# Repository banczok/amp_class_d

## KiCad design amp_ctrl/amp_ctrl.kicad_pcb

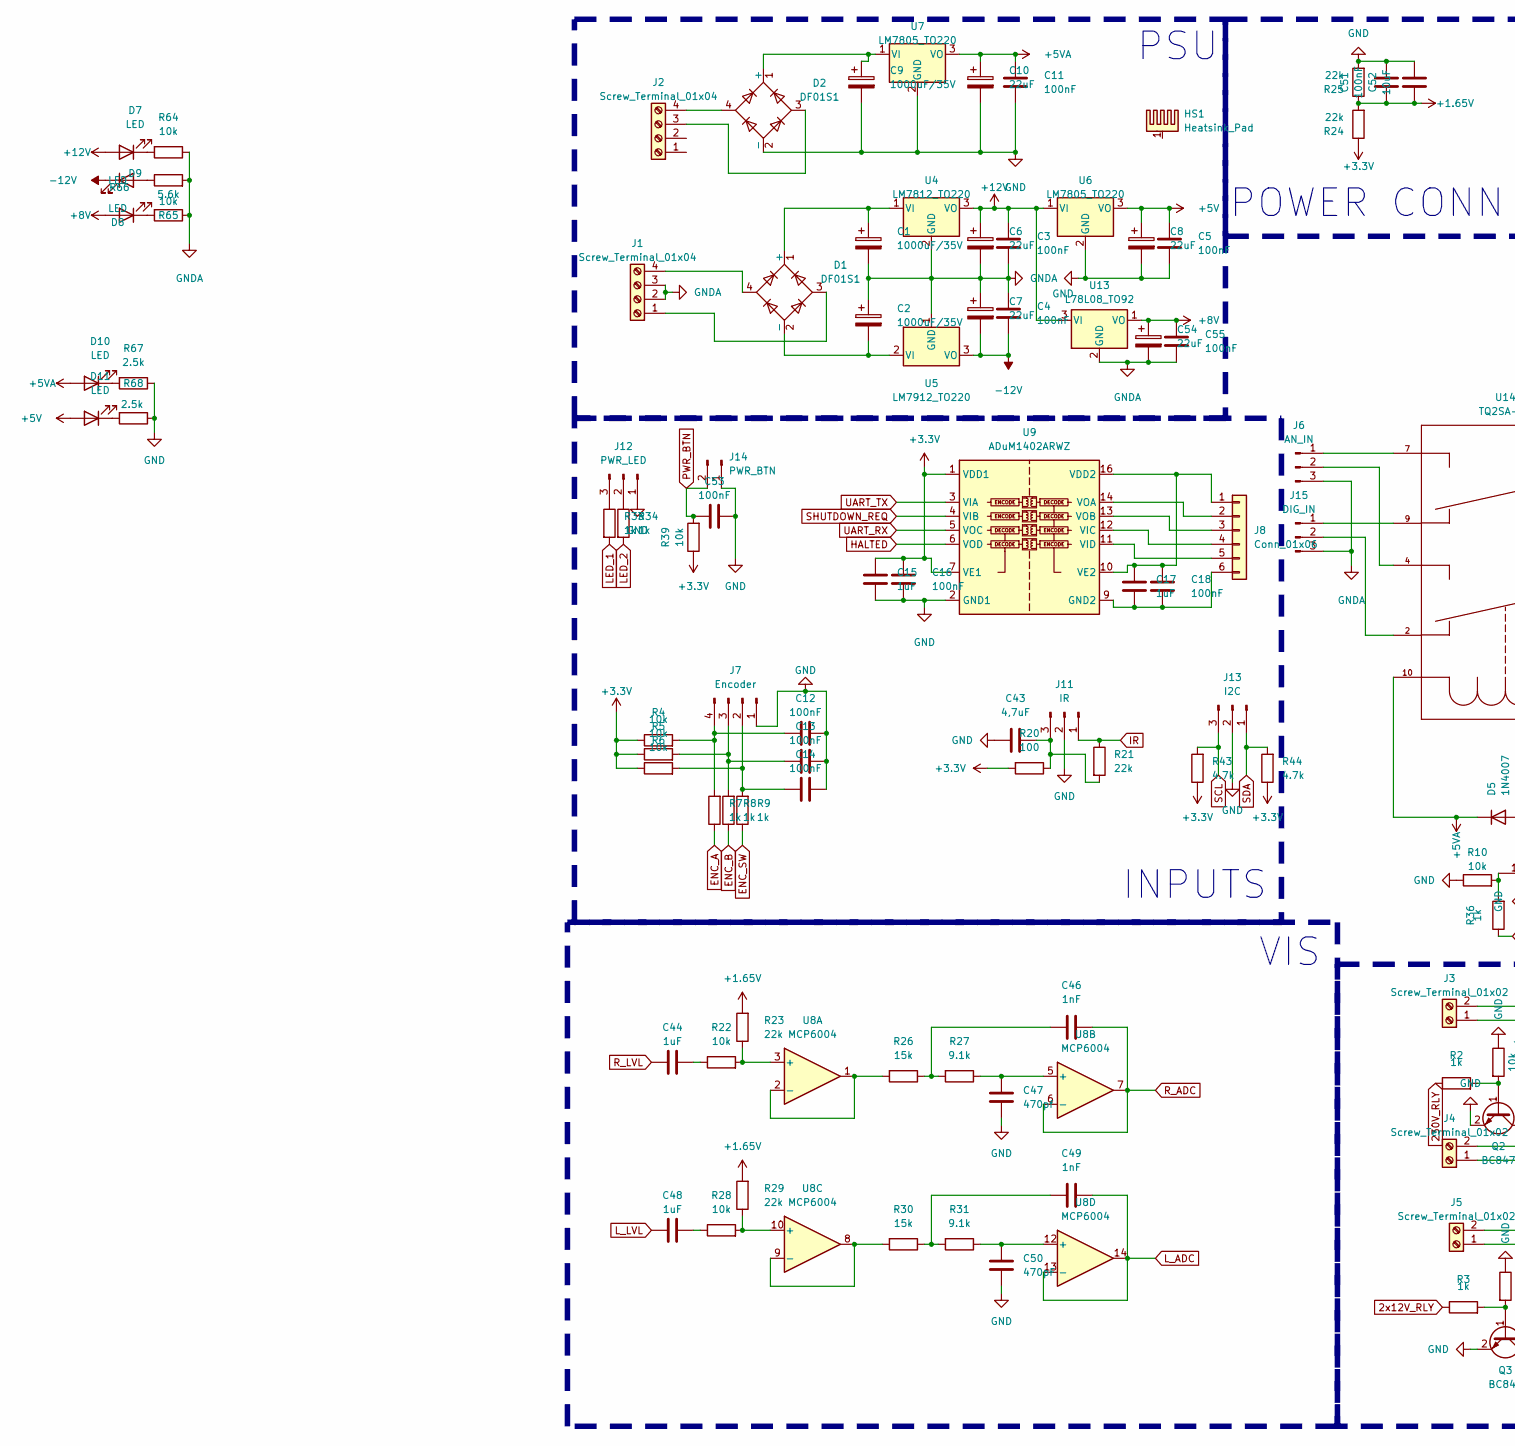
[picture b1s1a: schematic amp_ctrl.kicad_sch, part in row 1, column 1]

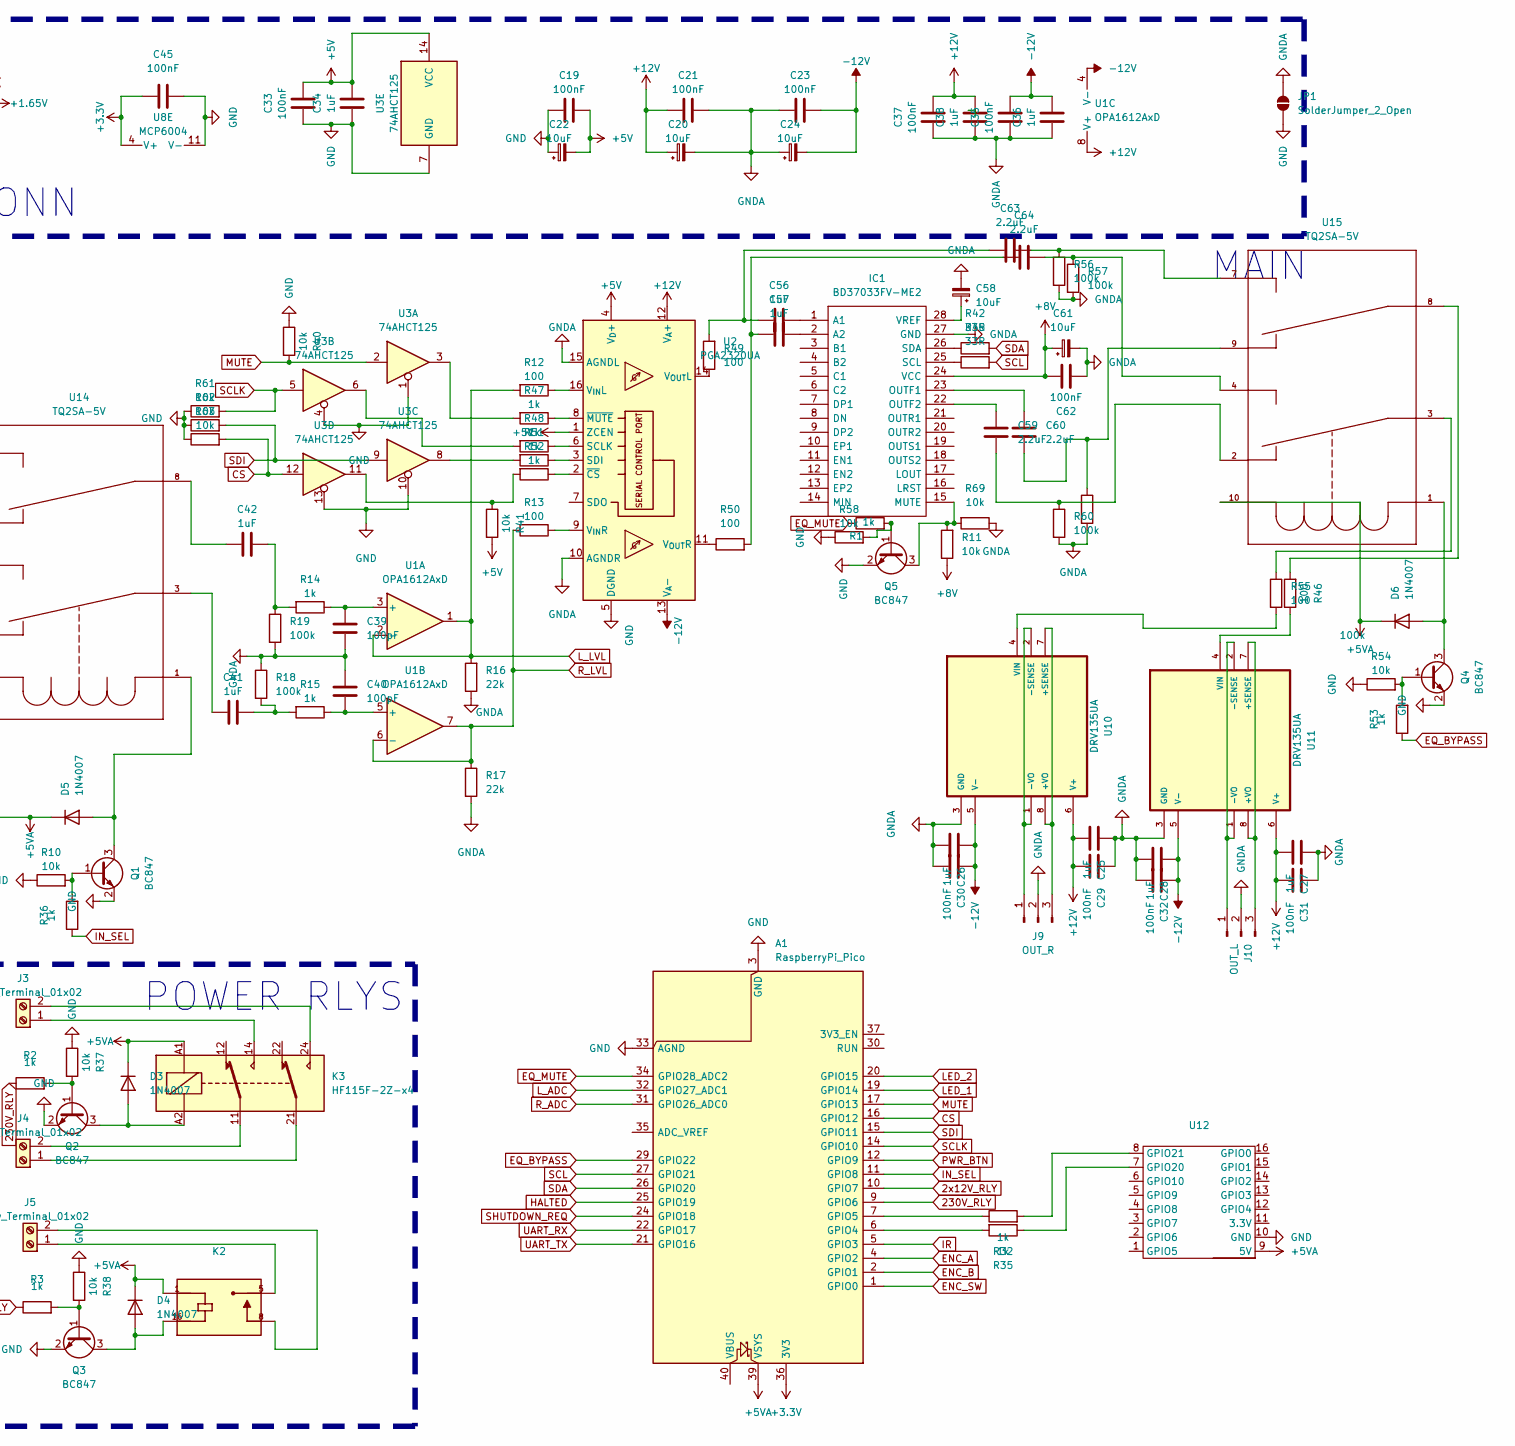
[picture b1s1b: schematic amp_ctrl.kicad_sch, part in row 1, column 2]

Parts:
A1: RaspberryPi_Pico; RaspberryPi_Pico_Common_SMD
C1, C2, C9: 1000uF/35V; CP_Radial_D12.5mm_P5.00mm
C3, C4, C5, C11, C12, C13, C14, C16, C18, C19, C21, C23, C29, C30, C31, C32, C33, C35, C37, C45, C51, C53, C55, C62: 100nF; C_0805_2012Metric_Pad1.18x1.45mm_HandSolder
C6, C7, C8, C10, C54: 22uF; CP_Radial_D5.0mm_P2.50mm
C15, C17, C25, C26, C27, C28, C34, C36, C38: 1uF; C_0805_2012Metric_Pad1.18x1.45mm_HandSolder
C20, C22, C24, C58, C61: 10uF; CP_EIA-6032-28_Kemet-C_Pad2.25x2.35mm_HandSolder
C39, C40: 100pF; C_0805_2012Metric_Pad1.18x1.45mm_HandSolder
C41, C42, C44, C48, C56, C57: 1uF; C_Disc_D8.0mm_W5.0mm_P5.00mm
C43: 4,7uF; C_0805_2012Metric_Pad1.18x1.45mm_HandSolder
C46, C49: 1nF; C_0805_2012Metric_Pad1.18x1.45mm_HandSolder
C47: 470pf; C_0805_2012Metric_Pad1.18x1.45mm_HandSolder
C50: 470pF; C_0805_2012Metric_Pad1.18x1.45mm_HandSolder
C52: 10uF; C_0805_2012Metric_Pad1.18x1.45mm_HandSolder
C59, C60, C63, C64: 2.2uF; C_Disc_D8.0mm_W5.0mm_P5.00mm
D1, D2: DF01S1; Diode_Bridge_OnSemi_SDIP-4L
D3, D4, D5, D6: 1N4007; D_DO-41_SOD81_P10.16mm_Horizontal
D7, D8, D9, D10, D11: LED; LED_1206_3216Metric_Pad1.42x1.75mm_HandSolder
HS1: Heatsink_Pad; Heatsink_Fischer_SK104-STC-STIC_35x13mm_2xDrill2.5mm
IC1: BD37033FV-ME2; SSOP-28_5.3x10.2mm_P0.65mm; Mouser Part Number 755-BD37033FV-ME2
J1, J2: Screw_Terminal_01x04; TerminalBlock_Phoenix_MKDS-1,5-4_1x04_P5.00mm_Horizontal
J3, J4, J5: Screw_Terminal_01x02; TerminalBlock_MaiXu_MX126-5.0-02P_1x02_P5.00mm
J6: AN_IN; PinHeader_1x03_P2.54mm_Vertical
J7: Encoder; PinHeader_1x04_P2.54mm_Vertical
J8: Conn_01x06; PinHeader_1x06_P2.54mm_Vertical
J9: OUT_R; PinHeader_1x03_P2.54mm_Vertical
J10: OUT_L; PinHeader_1x03_P2.54mm_Vertical
J11: IR; PinHeader_1x03_P2.54mm_Vertical
J12: PWR_LED; PinHeader_1x03_P2.54mm_Vertical
J13: I2C; PinHeader_1x03_P2.54mm_Vertical
J14: PWR_BTN; PinSocket_1x02_P2.54mm_Vertical
J15: DIG_IN; PinHeader_1x03_P2.54mm_Vertical
JP1: SolderJumper_2_Open; SolderJumper-2_P1.3mm_Open_Pad1.0x1.5mm
K2: PR30-12V-450-1A; RELAY_PR30-12V-450-1A; PARTREV 1.0
K3: HF115F-2Z-x4; Relay_DPDT_Finder_40.62
Q1, Q2, Q3, Q4, Q5: BC847; SOT-23
R1, R2, R3, R7, R8, R9, R14, R15, R32, R33, R34, R35, R36, R47, R48, R51, R52, R53: 1k; R_0805_2012Metric_Pad1.20x1.40mm_HandSolder
R4, R5, R6, R10, R11, R22, R28, R37, R38, R39, R40, R41, R54, R58, R61, R62, R63, R64, R65, R69: 10k; R_0805_2012Metric_Pad1.20x1.40mm_HandSolder
R12, R13, R20, R46, R49, R50, R55: 100; R_0805_2012Metric_Pad1.20x1.40mm_HandSolder
R16, R17, R21, R23, R24, R25, R29: 22k; R_0805_2012Metric_Pad1.20x1.40mm_HandSolder
R18, R19, R56, R57, R59, R60: 100k; R_0805_2012Metric_Pad1.20x1.40mm_HandSolder
R26, R30: 15k; R_0805_2012Metric_Pad1.20x1.40mm_HandSolder
R27, R31: 9.1k; R_0805_2012Metric_Pad1.20x1.40mm_HandSolder
R42, R45: 33R; R_0805_2012Metric_Pad1.20x1.40mm_HandSolder
R43, R44: 4.7k; R_0805_2012Metric_Pad1.20x1.40mm_HandSolder
R66: 5.6k; R_0805_2012Metric_Pad1.20x1.40mm_HandSolder
R67, R68: 2.5k; R_0805_2012Metric_Pad1.20x1.40mm_HandSolder
U1: OPA1612AxD; SOIC-8_3.9x4.9mm_P1.27mm
U2: PGA2320UA; SOIC-16W_7.5x10.3mm_P1.27mm
U3: 74AHCT125; SOIC-14_3.9x8.7mm_P1.27mm
U4: LM7812_TO220; TO-220-3_Vertical
U5: LM7912_TO220; TO-220-3_Vertical
U6, U7: LM7805_TO220; TO-220-3_Vertical
U8: MCP6004; SOIC-14_3.9x8.7mm_P1.27mm
U9: ADuM1402ARWZ; SOIC-16W_7.5x10.3mm_P1.27mm
U10, U11: DRV135UA; SOIC-8_3.9x4.9mm_P1.27mm
U12: ESP_C3_SUPERMINI_MINE_SMD
U13: L78L08_TO92; TO-92_Inline
U14, U15: TQ2SA-5V; RELAY_TQ2_SA_PAN

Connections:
2x12V_RLY: A1.10 (GPIO7), R3.1
230V_RLY: A1.9 (GPIO6), R2.1
+1.65V: C51.1, C52.1, R23.2, R24.2, R25.1, R29.2
+3.3V: A1.36 (3V3), C15.1, C16.1, C45.1, R4.1, R5.1, R6.1, R20.2, R24.1, R39.1, R43.1, R44.1, U8.4 (V+), U9.1 (VDD1), U9.7 (VE1)
+5V: C5.1, C8.1, C19.1, C22.2, C33.1, C34.2, D11.2 (A), R41.2, U2.1 (ZCEN), U2.4 (V_{D}+), U3.14 (VCC), U6.3 (VO)
+5VA: A1.39 (VSYS), C10.1, C11.1, D3.1 (K), D4.1 (K), D5.1 (K), D6.1 (K), D10.2 (A), K2.1, K3.A1, U7.3 (VO), U12.9 (5V), U14.10, U15.10
+8V: C54.1, C55.1, C61.1, C62.1, D9.2 (A), IC1.24 (VCC), R11.1, U13.1 (VO)
+12V: C3.1, C6.1, C20.1, C21.2, C25.2, C27.2, C29.2, C31.2, C37.1, C38.2, D7.2 (A), U1.8 (V+), U2.12 (V_{A}+), U4.3 (VO), U6.1 (VI), U10.6 (V+), U11.6 (V+), U13.3 (VI)
-12V: C4.2, C7.2, C23.1, C24.2, C26.1, C28.1, C30.1, C32.1, C35.1, C36.2, D8.1 (K), U1.4 (V-), U2.13 (V_{A}-), U5.3 (VO), U10.5 (V-), U11.5 (V-)
CS: A1.16 (GPIO12), R63.2, U3.12
ENC_A: A1.4 (GPIO2), R7.1
ENC_B: A1.2 (GPIO1), R8.1
ENC_SW: A1.1 (GPIO0), R9.1
EQ_BYPASS: A1.29 (GPIO22), R53.1
EQ_MUTE: A1.34 (GPIO28_ADC2), R1.1
GND: A1.3 (GND), A1.8 (GND), A1.13 (GND), A1.18 (GND), A1.23 (GND), A1.28 (GND), A1.33 (AGND), A1.38 (GND), C5.2, C8.2, C9.2, C10.2, C11.2, C12.2, C13.2, C14.2, C15.2, C16.2, C19.2, C22.1, C33.2, C34.1, C43.2, C45.2, C47.2, C50.2, C51.2, C52.2, C53.2, D2.2 (-), J7.1, J11.2, J12.1, J13.2, J14.1, JP1.1 (A), Q1.2 (E), Q2.2 (E), Q3.2 (E), Q4.2 (E), Q5.2 (E), R10.1, R25.2, R37.1, R38.1, R40.1, R54.1, R58.1, R61.1, R62.1, R63.1, R67.1, R68.1, U2.5 (DGND), U3.1, U3.4, U3.7 (GND), U3.10, U3.13, U6.2 (GND), U7.2 (GND), U8.11 (V-), U9.2 (GND1), U9.8 (GND1), U12.10 (GND); also elsewhere on the board
GNDA: C1.2, C2.1, C3.2, C4.1, C6.2, C7.1, C20.2, C21.1, C23.2, C24.1, C25.1, C26.2, C27.1, C28.2, C29.1, C30.2, C31.1, C32.2, C35.2, C36.1, C37.2, C38.1, C39.2, C40.1, C54.2, C55.2, C58.2, C61.2, C62.2, IC1.27 (GND), J1.2, J1.3, J6.3, J9.2, J10.2, J15.3, JP1.2 (B), R16.1, R17.2, R18.1, R19.2, R56.2, R57.2, R59.2, R60.2, R64.1, R65.2, R66.1, R69.1, U2.10 (AGNDR), U2.15 (AGNDL), U4.2 (GND), U5.1 (GND), U10.3 (GND), U11.3 (GND), U13.2 (GND); also elsewhere on the board
HALTED: A1.25 (GPIO19), U9.6 (VOD)
IN_SEL: A1.11 (GPIO8), R36.1
IR: A1.5 (GPIO3), J11.1, R21.1; also elsewhere on the board
LED_1: A1.19 (GPIO14), R33.2
LED_2: A1.20 (GPIO15), R34.2
L_ADC: A1.32 (GPIO27_ADC1), C49.1, U8.13 (-), U8.14
L_LVL: C48.1, R12.2, R16.2, U1.1, U1.2 (-)
MUTE: A1.17 (GPIO13), R40.2, U3.2
unnamed: A1.6 (GPIO4), R35.2
unnamed: A1.7 (GPIO5), R32.1
unnamed: C41.1, U14.3
unnamed: C41.2, R15.2, R18.2
unnamed: C42.1, U14.8
unnamed: C42.2, R14.2, R19.1
unnamed: C44.2, R22.1
unnamed: C46.2, R26.1, R27.2
unnamed: C48.2, R28.1
unnamed: C49.2, R30.1, R31.2
unnamed: C56.1, C63.2, R49.2
unnamed: C57.1, C64.2, R50.2
unnamed: C59.1, R60.1, U15.2
unnamed: C60.1, R59.1, U15.9
unnamed: C63.1, R56.1, U15.7
unnamed: C64.1, R57.1, U15.4
unnamed: C1.1, D1.1 (+), U4.1 (VI)
unnamed: C2.2, D1.2 (-), U5.2 (VI)
unnamed: C9.1, D2.1 (+), U7.1 (VI)
unnamed: D3.2 (A), K3.A2, Q2.3 (C)
unnamed: D4.2 (A), K2.16, Q3.3 (C)
unnamed: D5.2 (A), Q1.3 (C), U14.1
unnamed: D6.2 (A), Q4.3 (C), U15.1
unnamed: D7.1 (K), R64.2
unnamed: D8.2 (A), R65.1
unnamed: D9.1 (K), R66.2
unnamed: D10.1 (K), R67.2
unnamed: D11.1 (K), R68.2
unnamed: C56.2, IC1.1 (A1)
unnamed: C57.2, IC1.2 (A2)
unnamed: IC1.15 (MUTE), Q5.3 (C), R11.2, R69.2
unnamed: C60.2, IC1.23 (OUTF1)
unnamed: C59.2, IC1.22 (OUTF2)
unnamed: IC1.25 (SCL), R45.1
unnamed: IC1.26 (SDA), R42.1
unnamed: C58.1, IC1.28 (VREF)
unnamed 61: D1.3, J1.1; also elsewhere on the board
unnamed 62: D1.4, J1.4; also elsewhere on the board
unnamed 63: D2.3, J2.3; also elsewhere on the board
unnamed 64: D2.4, J2.4; also elsewhere on the board
unnamed 65: J3.1, K3.14; also elsewhere on the board
unnamed 66: J3.2, K3.24; also elsewhere on the board
unnamed 67: J4.1, K3.21; also elsewhere on the board
unnamed 68: J4.2, K3.11; also elsewhere on the board
unnamed 69: J5.1, K2.5; also elsewhere on the board
unnamed 70: J5.2, K2.8; also elsewhere on the board
unnamed 71: J6.1, U14.7; also elsewhere on the board
unnamed 72: J6.2, U14.4; also elsewhere on the board
unnamed 73: C14.1, J7.2, R6.2, R9.2; also elsewhere on the board
unnamed 74: C13.1, J7.3, R5.2, R8.2; also elsewhere on the board
unnamed 75: C12.1, J7.4, R4.2, R7.2; also elsewhere on the board
unnamed 76: C17.1, C18.1, J8.1, U9.10 (VE2), U9.16 (VDD2); also elsewhere on the board
unnamed 77: J8.2, U9.14 (VOA); also elsewhere on the board
unnamed 78: J8.3, U9.13 (VOB); also elsewhere on the board
unnamed 79: J8.4, U9.12 (VIC); also elsewhere on the board
unnamed 80: J8.5, U9.11 (VID); also elsewhere on the board
unnamed 81: C17.2, C18.2, J8.6, U9.9 (GND2), U9.15 (GND2); also elsewhere on the board
unnamed 82: J9.1, U10.1 (-VO), U10.2 (-SENSE); also elsewhere on the board
unnamed 83: J9.3, U10.7 (+SENSE), U10.8 (+VO); also elsewhere on the board
unnamed 84: J10.1, U11.1 (-VO), U11.2 (-SENSE); also elsewhere on the board
unnamed 85: J10.3, U11.7 (+SENSE), U11.8 (+VO); also elsewhere on the board
unnamed 86: C43.1, J11.3, R20.1, R21.2; also elsewhere on the board
unnamed 87: J12.2, R34.1; also elsewhere on the board
unnamed 88: J12.3, R33.1; also elsewhere on the board
unnamed 89: J15.1, U14.9; also elsewhere on the board
unnamed 90: J15.2, U14.2; also elsewhere on the board
unnamed: Q1.1 (B), R10.2, R36.2
unnamed: Q2.1 (B), R2.2, R37.2
unnamed: Q3.1 (B), R3.2, R38.2
unnamed: Q4.1 (B), R53.2, R54.2
unnamed: Q5.1 (B), R1.2, R58.2
unnamed: R41.1, R52.2, U3.11
unnamed: R46.2, U15.8
unnamed: R47.2, U3.3
unnamed: R48.2, U3.6
unnamed: R51.2, U3.8
unnamed: R55.1, U15.3
unnamed: C39.1, R14.1, U1.3 (+)
unnamed: C40.2, R15.1, U1.5 (+)
unnamed: R48.1, U2.6 (SCLK)
unnamed: R51.1, U2.3 (SDI)
unnamed: R12.1, U2.16 (V_{IN}L)
unnamed: R13.1, U2.9 (V_{IN}R)
unnamed: R49.1, U2.14 (V_{OUT}L)
unnamed: R50.1, U2.11 (V_{OUT}R)
unnamed: R52.1, U2.2 (~CS)
unnamed: R47.1, U2.8 (~MUTE)
unnamed: R22.2, R23.1, U8.3 (+)
unnamed: R26.2, U8.1, U8.2 (-)
unnamed: C47.1, R27.1, U8.5 (+)
unnamed: R28.2, R29.1, U8.10 (+)
unnamed: R30.2, U8.8, U8.9 (-)
unnamed: C50.1, R31.1, U8.12 (+)
unnamed: R55.2, U10.4 (VIN)
unnamed: R46.1, U11.4 (VIN)
unnamed: R35.1, U12.7 (GPIO20)
unnamed: R32.2, U12.8 (GPIO21)
PWR_BTN: A1.12 (GPIO9), C53.1, J14.2, R39.2; also elsewhere on the board
R_ADC: A1.31 (GPIO26_ADC0), C46.1, U8.6 (-), U8.7
R_LVL: C44.1, R13.2, R17.1, U1.6 (-), U1.7
SCL: A1.27 (GPIO21), J13.3, R43.2, R45.2; also elsewhere on the board
SCLK: A1.14 (GPIO10), R61.2, U3.5
SDA: A1.26 (GPIO20), J13.1, R42.2, R44.2; also elsewhere on the board
SDI: A1.15 (GPIO11), R62.2, U3.9
SHUTDOWN_REQ: A1.24 (GPIO18), U9.4 (VIB)
UART_RX: A1.22 (GPIO17), U9.5 (VOC)
UART_TX: A1.21 (GPIO16), U9.3 (VIA)

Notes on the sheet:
VIS
PSU
POWER CONN
MAIN
POWER RLYS
INPUTS

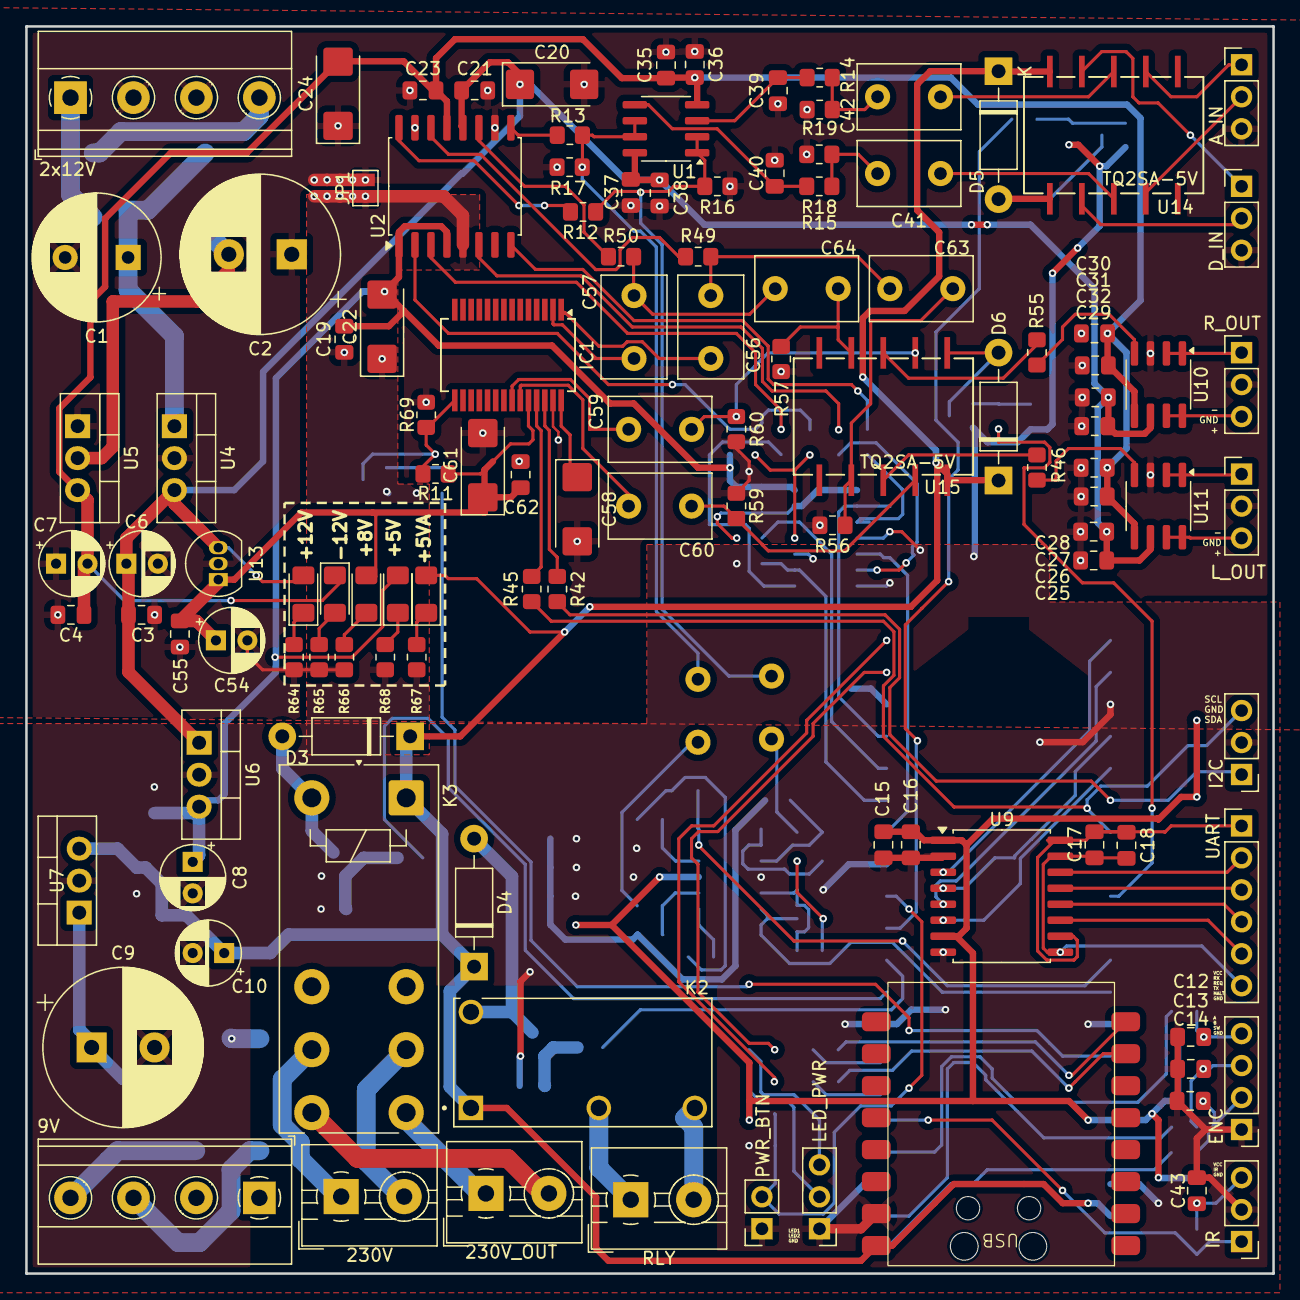
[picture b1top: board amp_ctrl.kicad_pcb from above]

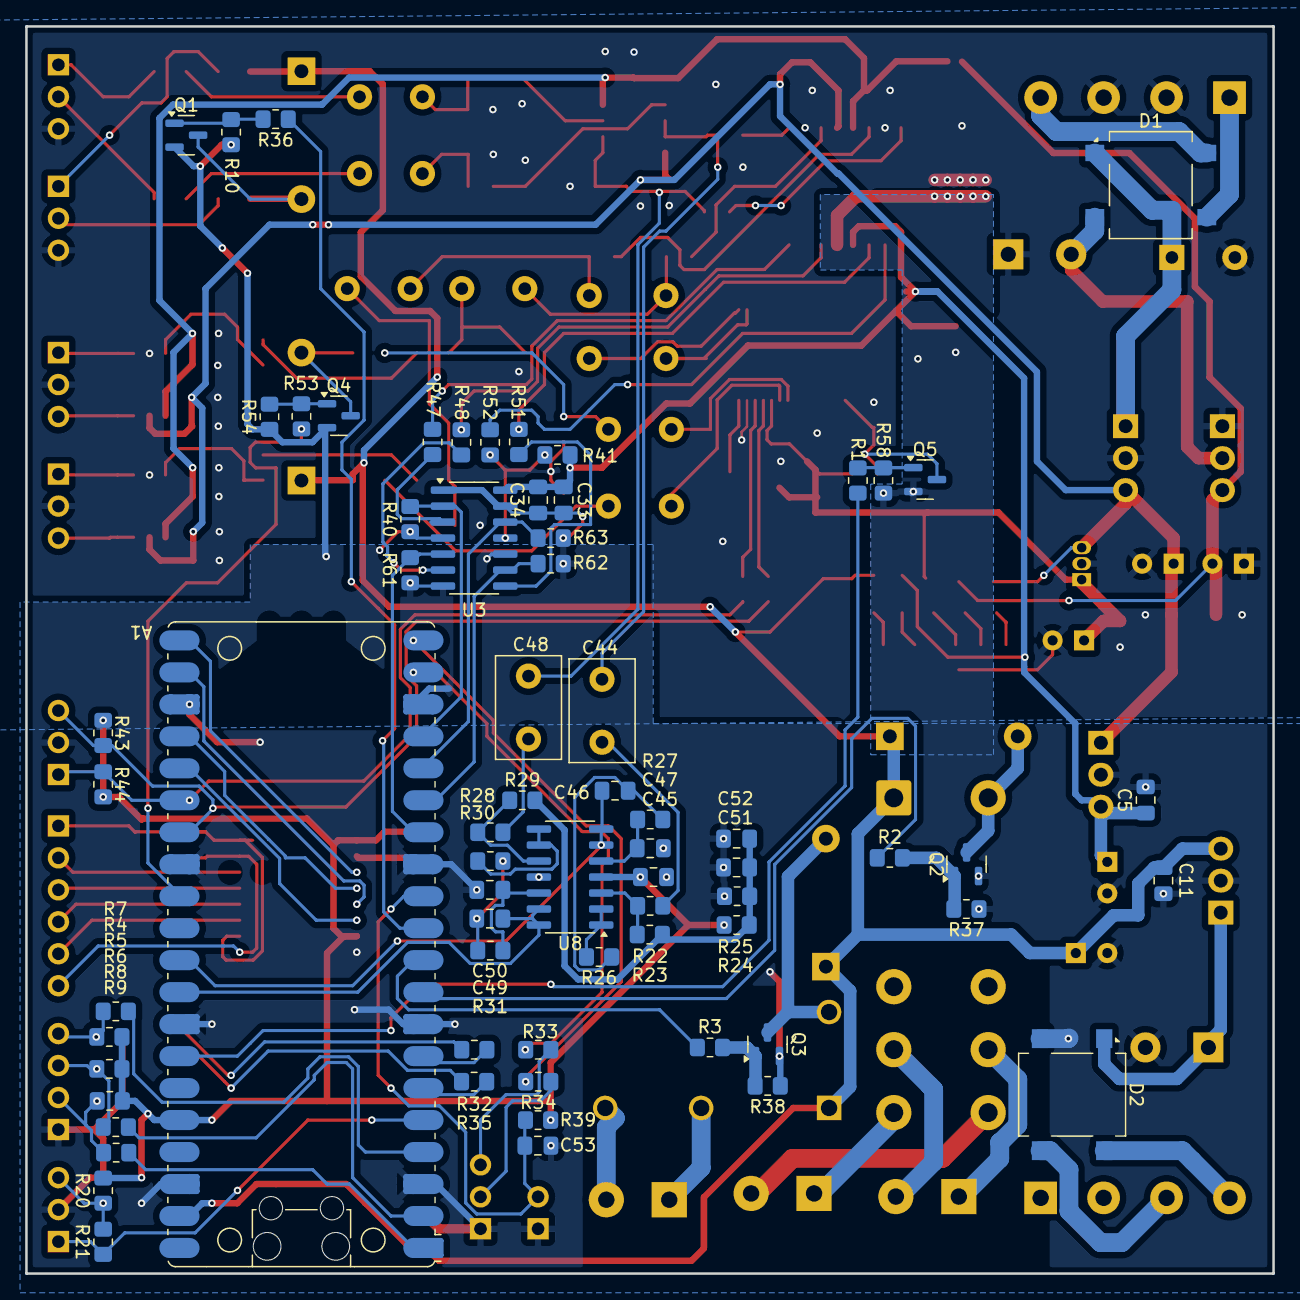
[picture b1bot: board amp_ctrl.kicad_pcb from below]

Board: 4 copper layers, 99.1 x 99.1 mm, 184 parts (68 on the bottom side), 132 nets.

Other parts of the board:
2x12V, 9V: Screw_Terminal_01x04; TerminalBlock_Phoenix_MKDS-1,5-4_1x04_P5.00mm_Horizontal
230V, 230V_OUT: Screw_Terminal_01x02; TerminalBlock_MaiXu_MX126-5.0-02P_1x02_P5.00mm
A_IN: AN_IN; PinHeader_1x03_P2.54mm_Vertical
D_IN: DIG_IN; PinHeader_1x03_P2.54mm_Vertical
ENC: Encoder; PinHeader_1x04_P2.54mm_Vertical
I2C: I2C; PinHeader_1x03_P2.54mm_Vertical
IR: IR; PinHeader_1x03_P2.54mm_Vertical
LED_PWR: PWR_LED; PinHeader_1x03_P2.54mm_Vertical
L_OUT: OUT_L; PinHeader_1x03_P2.54mm_Vertical
PWR_BTN: PWR_BTN; PinSocket_1x02_P2.54mm_Vertical
RLY: Screw_Terminal_01x02; TerminalBlock_MaiXu_MX126-5.0-02P_1x02_P5.00mm
R_OUT: OUT_R; PinHeader_1x03_P2.54mm_Vertical
UART: Conn_01x06; PinHeader_1x06_P2.54mm_Vertical

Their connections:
GND: ENC.1, I2C.2, IR.2, LED_PWR.1, PWR_BTN.1; also elsewhere on the board
GNDA: 2x12V.2, 2x12V.3, A_IN.3, D_IN.3, L_OUT.2, R_OUT.2; also elsewhere on the board
IR: IR.1; also elsewhere on the board
unnamed 61: 2x12V.1; also elsewhere on the board
unnamed 62: 2x12V.4; also elsewhere on the board
unnamed 63: 9V.3; also elsewhere on the board
unnamed 64: 9V.4; also elsewhere on the board
unnamed 65: 230V_OUT.1; also elsewhere on the board
unnamed 66: 230V_OUT.2; also elsewhere on the board
unnamed 67: 230V.1; also elsewhere on the board
unnamed 68: 230V.2; also elsewhere on the board
unnamed 69: RLY.1; also elsewhere on the board
unnamed 70: RLY.2; also elsewhere on the board
unnamed 71: A_IN.1; also elsewhere on the board
unnamed 72: A_IN.2; also elsewhere on the board
unnamed 73: ENC.2; also elsewhere on the board
unnamed 74: ENC.3; also elsewhere on the board
unnamed 75: ENC.4; also elsewhere on the board
unnamed 76: UART.1; also elsewhere on the board
unnamed 77: UART.2; also elsewhere on the board
unnamed 78: UART.3; also elsewhere on the board
unnamed 79: UART.4; also elsewhere on the board
unnamed 80: UART.5; also elsewhere on the board
unnamed 81: UART.6; also elsewhere on the board
unnamed 82: R_OUT.1; also elsewhere on the board
unnamed 83: R_OUT.3; also elsewhere on the board
unnamed 84: L_OUT.1; also elsewhere on the board
unnamed 85: L_OUT.3; also elsewhere on the board
unnamed 86: IR.3; also elsewhere on the board
unnamed 87: LED_PWR.2; also elsewhere on the board
unnamed 88: LED_PWR.3; also elsewhere on the board
unnamed 89: D_IN.1; also elsewhere on the board
unnamed 90: D_IN.2; also elsewhere on the board
PWR_BTN: PWR_BTN.2; also elsewhere on the board
SCL: I2C.3; also elsewhere on the board
SDA: I2C.1; also elsewhere on the board

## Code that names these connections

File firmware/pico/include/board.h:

/* board.h - pin map and hardware constants for the preamp controller.
 *
 * Target: Raspberry Pi Pico 2 (RP2350A) on amp_ctrl rev A.
 * Every pin below was taken from the KiCad netlist, not from memory.
 */
#ifndef BOARD_H
#define BOARD_H

#include "hardware/spi.h"
#include "hardware/i2c.h"
#include "hardware/uart.h"

/* ---------------------------------------------------------------- pins */

/* Rotary encoder.  All three have a 10k pull-up to +3V3, a 1k series
 * resistor and 100n to ground, so they are active-low and already
 * debounced with tau ~ 1 ms.  No internal pulls needed - and note the
 * RP2350-E9 erratum makes internal pull-downs unreliable anyway. */
#define PIN_ENC_SW        0
#define PIN_ENC_B         1
#define PIN_ENC_A         2

/* IR receiver (TSOP-class, open-collector, 22k pull-up on the board). */
#define PIN_IR            3

/* UART1 -> ESP32-C3 SuperMini.  Pico GP4 drives the ESP's GPIO20/U0RXD,
 * Pico GP5 listens to the ESP's GPIO21/U0TXD. */
#define PIN_ESP_TX        4
#define PIN_ESP_RX        5
#define UART_ESP          uart1
#define UART_ESP_BAUD     115200

/* Relay drives.  All four are NPN low-side (BC847) with a 10k base
 * pull-down, so GPIO low == coil de-energised == the reset state. */
#define PIN_RLY_MAINS     6    /* K3  230 V, 2 pole                       */
#define PIN_RLY_SECONDARY 7    /* K2  T1 2x12 V secondary                 */
#define PIN_RLY_INPUT     8    /* U14 input select                        */
#define PIN_RLY_EQ_BYPASS 22   /* U15 EQ bypass                           */

/* Front-panel power button: 10k pull-up + 100n, active low. */
#define PIN_PWR_BTN       9

/* PGA2320 three-wire port.  These four GPIOs feed the 74AHCT125 level
 * shifter (U3); the AHCT outputs drive the PGA at 5 V. */
#define PIN_PGA_SCLK      10
#define PIN_PGA_SDI       11
#define PIN_PGA_CS        12
#define PIN_PGA_MUTE      13   /* PGA ~MUTE, active LOW  -> low = muted   */
#define PGA_SPI           spi1
#define PGA_SPI_BAUD      1000000

/* Status LEDs, external, 1k series, ~1.3 mA. */
#define PIN_LED_1         14
#define PIN_LED_2         15

/* UART0 -> Raspberry Pi through the ADuM/ISO7742 isolator. */
#define PIN_PI_TX         16
#define PIN_PI_RX         17
#define UART_PI           uart0
#define UART_PI_BAUD      921600

/* Discrete handshake lines to the Pi, also through the isolator. */
#define PIN_SHUTDOWN_REQ  18   /* out: assert to ask the Pi to halt       */
#define PIN_HALTED        19   /* in : Pi asserts when it has halted      */

/* I2C to the BD37033 (and out to header J13). 33R series on both lines,
 * 4k7 pull-ups at the Pico end. */
#define PIN_SDA           20
#define PIN_SCL           21
#define BD_I2C            i2c0
#define BD_I2C_BAUD       100000

/* Metering ADC inputs, fed from the MCP6004 Sallen-Key stage, biased
 * at 1.65 V.  ADC0 = right, ADC1 = left. */
#define PIN_ADC_R         26
#define PIN_ADC_L         27
#define ADC_CH_R          0
#define ADC_CH_L          1

/* BD37033 hardware MUTE via Q5 (NPN, open collector on IC1 pin 15).
 * GPIO HIGH -> Q5 on -> MUTE pin pulled low -> chip MUTED. */
#define PIN_BD_MUTE       28

/* --------------------------------------------------- logical polarity */

/* U14 input select.  De-energised (coil off, GPIO low) selects the DAC. */
#define IN_SEL_DIGITAL    0
#define IN_SEL_ANALOG     1

/* U15 EQ bypass.  De-energised keeps the BD37033 in circuit, so the coil
 * is unpowered during normal listening. */
#define EQ_PATH_ACTIVE    0
#define EQ_PATH_BYPASS    1

/* Q5 sense for the BD37033 mute pin. */
#define BD_MUTE_ON        1
#define BD_MUTE_OFF       0

/* --------------------------------------------------- audio constants  */

/* PGA2320: gain(dB) = 31.5 - 0.5 * (255 - N), N=0 is mute.
 * N = 192 is therefore exactly 0 dB, which is the hardware ceiling the
 * design doc mandates - the positive-gain range is noisy and never
 * needed here. */
#define PGA_CODE_MUTE     0
#define PGA_CODE_MIN      1      /* -95.5 dB */
#define PGA_CODE_0DB      192
#define PGA_CODE_MAX      PGA_CODE_0DB
#define PGA_DB_PER_STEP   0.5f

static inline float pga_code_to_db(int code) {
    return PGA_DB_PER_STEP * (float)(code - PGA_CODE_0DB);
}
static inline int pga_db_to_code(float db) {
    int c = PGA_CODE_0DB + (int)(db / PGA_DB_PER_STEP + (db < 0 ? -0.5f : 0.5f));
    if (c > PGA_CODE_MAX) c = PGA_CODE_MAX;
    if (c < PGA_CODE_MIN) c = PGA_CODE_MIN;
    return c;
}

/* EQ boost headroom.  From the design doc:
 *     max_boost = min(15, -3 - pga_dB)
 * The chain delivers 2.12 V differential at PGA 0 dB against the amp's
 * 3.05 V full output, i.e. 3.15 dB of headroom - so any boost at full
 * volume clips the amplifier, not the preamp.  Floored at 0: we never
 * *force* a cut, we just refuse to boost. */
static inline float eq_max_boost_db(float pga_db) {
    float m = -3.0f - pga_db;
    if (m > 15.0f) m = 15.0f;
    if (m < 0.0f)  m = 0.0f;
    return m;
}

/* Sequencing timings, from the design doc. */
#define T_MAINS_TO_SECONDARY_MS   400
#define T_RAILS_SETTLE_MS         600
#define T_UNMUTE_DELAY_MS        2500
#define T_MUTE_BEFORE_SHUTDOWN_MS 200
#define T_PI_HALT_TIMEOUT_MS    30000
#define T_SECONDARY_TO_MAINS_MS   300

/* Long-press threshold for the encoder button -> settings menu. */
#define T_ENC_LONGPRESS_MS       1200
#define T_PWR_LONGPRESS_MS       1500

#endif /* BOARD_H */

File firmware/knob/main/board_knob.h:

/* board_knob.h - VIEWE UEDX48480021-MD80ESP32, 2.1" 480x480 round.
 *
 * ESP32-S3-R8: 16 MB flash, 8 MB octal PSRAM.
 * ST7701S over 3-wire SPI for setup, 16-bit parallel RGB for pixels.
 * CST816-class capacitive touch on I2C0.
 * Rotary encoder on GPIO6/5, its push on GPIO0.
 *
 * Every number here comes from the vendor BSP
 * (examples/ESP-IDF/DX48480021ET-WB-A-LVGL/components/bsp/include/bsp/esp-bsp.h),
 * not from a datasheet guess.  The RGB timings in particular are the
 * touch-enabled variant: 18 MHz pixel clock, because the touch
 * controller shares enough of the ground plane that the 20 MHz timing
 * used on the touchless board couples into it.
 */
#ifndef BOARD_KNOB_H
#define BOARD_KNOB_H

#include "driver/gpio.h"
#include "driver/i2c.h"

/* ------------------------------------------------------------ display */

#define LCD_H_RES            480
#define LCD_V_RES            480
#define LCD_PIXEL_CLOCK_HZ   (18 * 1000 * 1000)

#define LCD_HSYNC_PULSE       8
#define LCD_HSYNC_BACK        20
#define LCD_HSYNC_FRONT       40
#define LCD_VSYNC_PULSE       8
#define LCD_VSYNC_BACK        20
#define LCD_VSYNC_FRONT       50

#define PIN_LCD_VSYNC        GPIO_NUM_3
#define PIN_LCD_HSYNC        GPIO_NUM_46
#define PIN_LCD_DE           GPIO_NUM_17
#define PIN_LCD_PCLK         GPIO_NUM_9
#define PIN_LCD_RST          GPIO_NUM_8
#define PIN_LCD_BL           GPIO_NUM_7

/* 16-bit RGB565 bus, in the order the panel expects. */
#define PIN_LCD_DATA0        GPIO_NUM_10   /* B3 */
#define PIN_LCD_DATA1        GPIO_NUM_11   /* B4 */
#define PIN_LCD_DATA2        GPIO_NUM_12   /* B5 */
#define PIN_LCD_DATA3        GPIO_NUM_13   /* B6 */
#define PIN_LCD_DATA4        GPIO_NUM_14   /* B7 */
#define PIN_LCD_DATA5        GPIO_NUM_21   /* G2 */
#define PIN_LCD_DATA6        GPIO_NUM_47   /* G3 */
#define PIN_LCD_DATA7        GPIO_NUM_48   /* G4 */
#define PIN_LCD_DATA8        GPIO_NUM_45   /* G5 */
#define PIN_LCD_DATA9        GPIO_NUM_38   /* G6 */
#define PIN_LCD_DATA10       GPIO_NUM_39   /* G7 */
#define PIN_LCD_DATA11       GPIO_NUM_40   /* R3 */
#define PIN_LCD_DATA12       GPIO_NUM_41   /* R4 */
#define PIN_LCD_DATA13       GPIO_NUM_42   /* R5 */
#define PIN_LCD_DATA14       GPIO_NUM_2    /* R6 */
#define PIN_LCD_DATA15       GPIO_NUM_1    /* R7 */

/* 3-wire SPI, used only for the ST7701S init sequence.  SCK and SDO are
 * shared with DATA3 and DATA2 - the panel tri-states them once the RGB
 * bus starts, which is why the init has to complete first. */
#define PIN_LCD_SPI_CS       GPIO_NUM_18
#define PIN_LCD_SPI_SCK      GPIO_NUM_13
#define PIN_LCD_SPI_SDO      GPIO_NUM_12

/* -------------------------------------------------------------- touch */

#define TOUCH_I2C_PORT       I2C_NUM_0
#define PIN_TOUCH_SCL        GPIO_NUM_15
#define PIN_TOUCH_SDA        GPIO_NUM_16
#define PIN_TOUCH_RST        GPIO_NUM_NC
#define PIN_TOUCH_INT        GPIO_NUM_NC   /* not brought out on this board */

/* ------------------------------------------------------------- inputs */

#define PIN_ENC_A            GPIO_NUM_6
#define PIN_ENC_B            GPIO_NUM_5

/* The knob press.  Shared with BOOT, active low, and - the reason it can
 * be the wake source at all - an RTC GPIO, so ext0 can watch it while
 * the whole digital domain is powered down.  Touch cannot do this: this
 * board does not bring TP_INT out, so the touch controller can only be
 * polled over I2C, which needs the CPU running. */
#define PIN_BTN              GPIO_NUM_0
#define BTN_ACTIVE_LEVEL     0

/* Neither the phases nor the button has an external pull-up: on the
 * vendor schematic PHA/PHB go straight to the encoder contacts and then
 * to ground, and R14/R15 (4k7) are the touch I2C pull-ups, not these.
 * So the internal pull-ups are load-bearing, awake and asleep alike.
 * The debounce footprints C10/C11 on PHA/PHB are marked NC and are not
 * fitted, which is why the Gray-code decoder does all the filtering. */

/* Wake on turning the knob as well as pressing it.
 *
 * Off by default, and not only to avoid knocks waking it: the first
 * detent is unrecoverable.  Quadrature needs two edges to know which way
 * it went and the CPU is not running for the first one, so a turn from
 * cold brings the screen up showing the current volume and only the
 * second detent onward moves it.
 *
 * Cost depends on where your encoder rests.  If its detent leaves both
 * contacts open - most EC11-style parts - this is free.  If a contact
 * rests closed, the internal pull-up (~45 kOhm) burns ~73 uA
 * continuously through it, which dwarfs everything else in the sleep
 * budget.  Measure before switching this on. */
#define WAKE_ON_ROTATION     0

/* ------------------------------------------------------- battery sense */

/* GPIO4 is ADC1_CH3.  ADC1 is not optional here: ADC2 shares its SAR with
 * the WiFi radio and reads fail outright while WiFi is up, which on this
 * device is exactly when you would want a battery reading.
 *
 * Divider from the LiPo positive terminal:
 *
 *     BAT+ ---[ R_TOP ]---+--- GPIO4
 *                         |
 *                      [ R_BOT ]   plus 100 nF to GND at the pin
 *                         |
 *                        GND
 *
 * The cap is not optional either.  The SAR samples onto a small internal
 * capacitor and needs a low source impedance to charge it; anything above
 * about 10 kOhm of Thevenin impedance reads low without a local reservoir
 * to sample against. */
#define PIN_VBAT             GPIO_NUM_4
#define VBAT_ADC_CHANNEL     ADC_CHANNEL_3
#define VBAT_ADC_UNIT        ADC_UNIT_1

/* Divider ratio as a per-mille integer: mV_battery = mV_pin * 1000 / this.
 * 500 is a 1:1 divider (two equal resistors).  Change this and nothing
 * else if you re-pick the resistors. */
#define VBAT_DIVIDER_PERMILLE  500

/* Deliberately NOT scaled to put 4.2 V near 3.0 V at the pin.  The S3's
 * 12 dB attenuation curve compresses toward the top of its ~3.1 V range,
 * so a 1.4:1 divider puts a full battery in the least accurate part of
 * the curve - and leaves no margin if a charger holds the cell above
 * 4.2 V.  A 1:1 divider lands 4.2 V at 2.1 V, in the linear region, and
 * still gives ~800 counts across the usable 3.3-4.2 V range. */

#define VBAT_SAMPLES         32     /* averaged                          */
#define VBAT_WARMUP_SAMPLES   4     /* discarded after the mux switches  */

/* ------------------------------------------------------------ timings */

#define T_POWER_HOLD_MS      2000   /* hold this long = power button      */
#define T_PROMPT_TIMEOUT_MS  6000   /* woken, amp off, nothing pressed    */

/* How long to keep asking before deciding the amplifier is not there.
 * The C3 answers a hello in about 5 ms when it is listening, so this is
 * not about its speed - it is about the cached channel being stale, which
 * costs a retry on another channel. */
#define T_LINK_WAIT_MS        900
#define T_LINK_RETRY_MS       250

/* A wake that found nothing is a wake the user did not get anything out
 * of, so it should cost as little as possible: dimmer, and brief. */
#define T_NOLINK_TIMEOUT_MS  4000
#define BL_NOLINK_PERCENT      22

/* The link is stale rather than dead until this long without a frame.
 *
 * This only works because of the keepalive below: the amplifier pushes
 * state when it changes, not on a schedule, so a quiet minute would look
 * exactly like an unplugged amplifier without something to ask.  The
 * keepalive has to be comfortably shorter than the stale window. */
#define T_LINK_STALE_MS      4000
#define T_LINK_KEEPALIVE_MS  1500
#define T_IDLE_TIMEOUT_MS   10000   /* awake with the amp on, but unused  */
#define T_VOL_OVERLAY_MS     1500   /* how long the volume ring lingers   */
#define T_BL_FADE_MS          200
#define BL_ACTIVE_PERCENT      40   /* bright enough indoors, easy on the
                                     * cell - the backlight is by far the
                                     * largest draw while awake          */

/* Knob detents are batched into one radio frame rather than sent one at
 * a time; this is how long we wait for the burst to end. */
#define T_KNOB_COALESCE_MS     60

#endif /* BOARD_KNOB_H */
